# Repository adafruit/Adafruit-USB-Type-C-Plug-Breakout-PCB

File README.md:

## Adafruit USB Type C Plug Breakout PCB

<a href="http://www.adafruit.com/products/5978"><br/>
Click here to purchase one from the Adafruit shop</a>

PCB files for the Adafruit USB Type C Plug Breakout. 

Format is EagleCAD schematic and board layout
* https://www.adafruit.com/product/5978

### Description

Throw out all those Mini and Micro B USB cables you have in a plastic bin - the next generation of USB connectors is here with USB C! You've seen these connectors pop up on all sorts of devices, as the industry moves from micro B or lightning to the new standard. Well, at least until the next standard comes out

USB C features a symmetric/reversible connector, more data pins and higher current output capability. But, for most developers, the pin usage you know and love from older USB will work just fine. This breakout gives you all the basics you need and a resistor configuration that will make sure you get 5V power. We chose a plug that has a semi-through hole mounting configuration that seems fairly mechanically stable. That said, it will not survive purposeful bending the way a Type A would.

There's one 5.1K resistor on the CC1 pin, so if you plug this into a computer or power supply, the upstream port to provide 5V and up to 1.5A. Whether the upstream can supply that much current depends on what you're connecting to.

Unlike USB Type C sockets, the plug side purposefully does not use both sets of D+/D-/CC pins: that's how the host figures out which way the cable is plugged. So, when you connect to the pads on the breakout, know that you're going to be on the 'A' side. The socket on the other end should be tying the data lines together for you.

For most usages, you can just connect VBUS to your 5V input, GND to ground, and D+ and D- as you expect.

### License

Adafruit invests time and resources providing this open source design, please support Adafruit and open-source hardware by purchasing products from [Adafruit](https://www.adafruit.com)!

Designed by Limor Fried/Ladyada for Adafruit Industries.

Creative Commons Attribution/Share-Alike, all text above must be included in any redistribution. 
See license.txt for additional details.

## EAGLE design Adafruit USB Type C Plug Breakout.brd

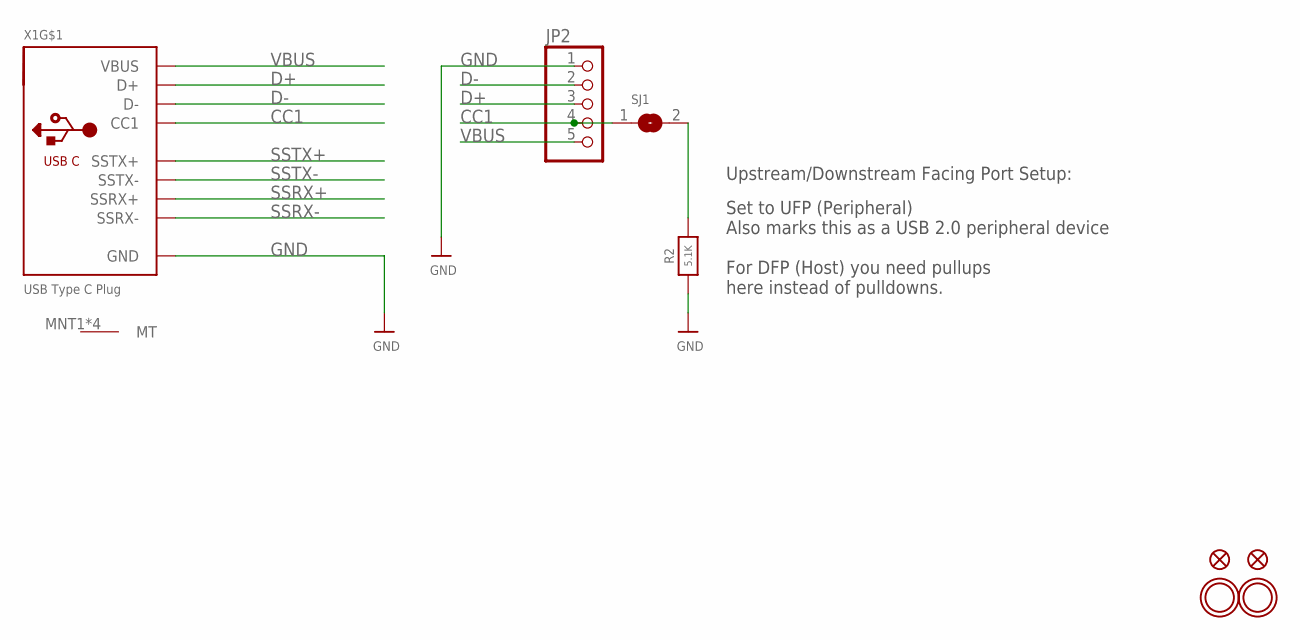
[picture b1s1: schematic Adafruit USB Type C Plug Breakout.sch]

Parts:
FID1, FID2: FIDUCIAL_0.5MM
JP2: HEADER-1X576MIL; 1X05_ROUND_76
R2: 5.1K; 0603-NO
SJ1: SOLDERJUMPERCLOSED; SOLDERJUMPER_CLOSEDWIRE
U$1, U$2: MOUNTINGHOLE2.5; MOUNTINGHOLE_2.5_PLATED
X1: USB Type C Plug; USB_TYPEC_PLUG_12P

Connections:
CC1: JP2.4, SJ1.1, X1.A5 (CC1)
D+: JP2.3, X1.A6 (D+)
D-: JP2.2, X1.A7 (D-)
GND: JP2.1, R2.1, X1.A1 (GND), X1.A12 (GND), X1.B12 (GND)
unnamed: R2.2, SJ1.2
SSRX+: X1.B11 (SSRX+)
SSRX-: X1.B10 (SSRX-)
SSTX+: X1.A2 (SSTX+)
SSTX-: X1.A3 (SSTX-)
VBUS: JP2.5, X1.A4 (VBUS), X1.B9 (VBUS)

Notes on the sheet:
Set to UFP (Peripheral) Also marks this as a USB 2.0 peripheral device For DFP (Host) you need pullups here instead of pulldowns.
Upstream/Downstream Facing Port Setup:

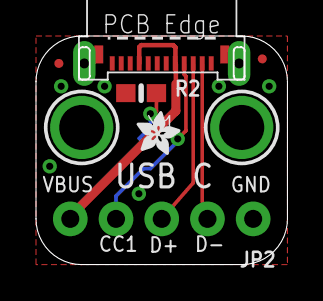
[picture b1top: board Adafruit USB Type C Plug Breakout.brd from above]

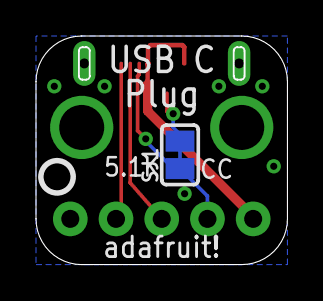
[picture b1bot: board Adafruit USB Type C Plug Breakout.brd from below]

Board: 2 copper layers, 13.9 x 12.6 mm, 10 parts (2 on the bottom side), 6 nets.

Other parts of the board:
U$3: ADAFRUIT_2.5MM
U$8: PCBFEAT-REV-040

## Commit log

2024-06-18 cookiecutter

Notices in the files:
parts and their libraries:
microbuilder: This work is placed in the public domain, and may be freely used for commercial and non-commercial work with the following conditions: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
